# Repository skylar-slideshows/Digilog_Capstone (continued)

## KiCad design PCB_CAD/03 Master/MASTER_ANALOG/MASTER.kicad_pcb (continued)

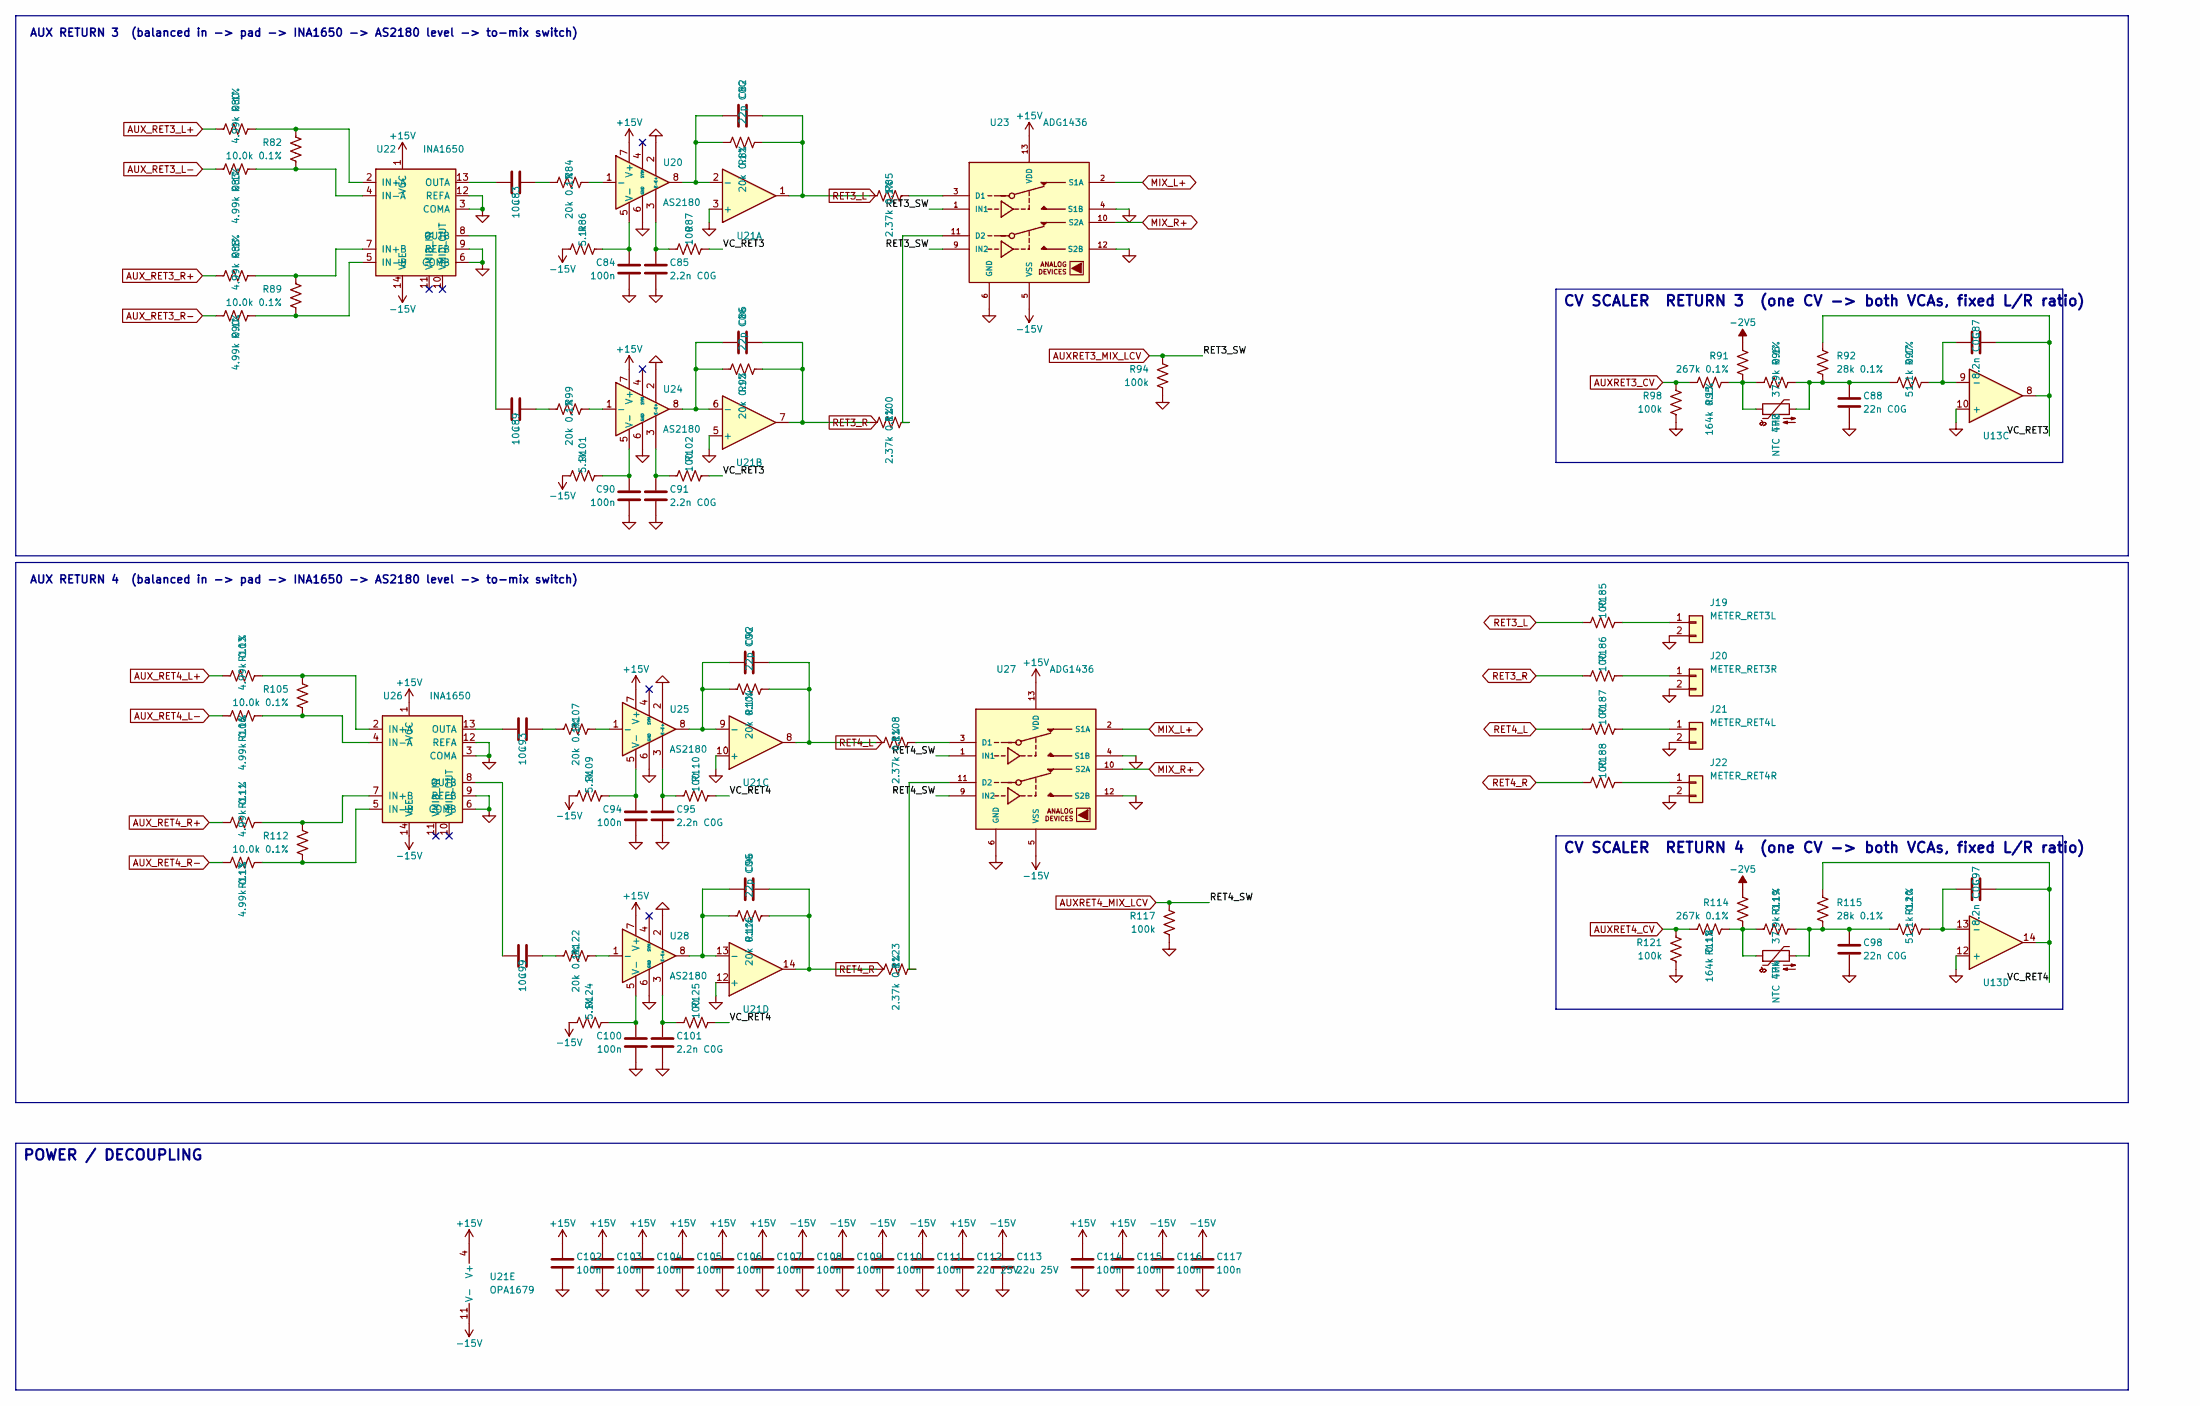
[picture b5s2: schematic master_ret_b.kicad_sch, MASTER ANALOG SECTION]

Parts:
C82, C86, C92, C96: 22p C0G; C_0603_1608Metric; LCSC C105620
C83, C89, C93, C99: 10u; CP_Elec_6.3x5.4_Nichicon; LCSC C340735
C84, C90, C94, C100, C102, C103, C104, C105, C106, C107, C108, C109, C110, C111, C114, C115, C116, C117: 100n; C_0603_1608Metric; LCSC C1590
C85, C91, C95, C101: 2.2n C0G; C_0603_1608Metric; LCSC C107043
C87, C97: 8.2n C0G; C_0805_2012Metric; LCSC C296107
C88, C98: 22n C0G; C_1206_3216Metric; LCSC C105982
C112, C113: 22u 25V; C_1210_3225Metric; LCSC C21397
J19: METER_RET3L; PinHeader_1x02_P2.54mm_Vertical; LCSC dnp
J20: METER_RET3R; PinHeader_1x02_P2.54mm_Vertical; LCSC dnp
J21: METER_RET4L; PinHeader_1x02_P2.54mm_Vertical; LCSC dnp
J22: METER_RET4R; PinHeader_1x02_P2.54mm_Vertical; LCSC dnp
R80, R83, R88, R90, R103, R106, R111, R113: 4.99k 0.1%; R_0603_1608Metric; LCSC C190614
R81, R84, R93, R99, R104, R107, R116, R122: 20k 0.1%; R_0603_1608Metric; LCSC C190611
R82, R89, R105, R112: 10.0k 0.1%; R_0603_1608Metric; LCSC C95204
R85, R100, R108, R123: 2.37k 0.1%; R_0603_1608Metric; LCSC C50670507
R86, R101, R109, R124: 5.1k; R_0603_1608Metric; LCSC C122969
R87, R102, R110, R125, R185, R186, R187, R188: 100; R_0603_1608Metric; LCSC C122970
R91, R114: 267k 0.1%; R_0603_1608Metric; LCSC C861785
R92, R115: 28k 0.1%; R_0603_1608Metric; LCSC C705756
R94, R98, R117, R121: 100k; R_0603_1608Metric; LCSC C122538
R95, R118: 164k 0.1%; R_0805_2012Metric; LCSC C865214
R96, R119: 37.9k 0.1%; R_0603_1608Metric; LCSC C861362
R97, R120: 51.1k 0.1%; R_0603_1608Metric; LCSC C491138
TH3, TH4: NTC 47k; R_Axial_DIN0207_L6.3mm_D2.5mm_P2.54mm_Vertical; LCSC dnp
U13: OPA4197; SOIC-14_3.9x8.7mm_P1.27mm; LCSC C2058532
U20, U24, U25, U28: AS2180; PinSocket_1x08_P2.54mm_Vertical; LCSC dnp
U21: OPA1679; TSSOP-14_4.4x5mm_P0.65mm; LCSC C2057264
U22, U26: INA1650; TSSOP-14_4.4x5mm_P0.65mm; LCSC C553130
U23, U27: ADG1436; TSSOP-16_4.4x5mm_P0.65mm; LCSC C408899

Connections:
+15V: C102.1, C103.1, C104.1, C105.1, C106.1, C107.1, C112.1, C114.1, C115.1, U20.7 (V+), U21.4 (V+), U22.1 (VCC), U23.13 (VDD), U24.7 (V+), U25.7 (V+), U26.1 (VCC), U27.13 (VDD), U28.7 (V+); also elsewhere on the board
-2V5: R91.1, R114.1; also elsewhere on the board
-15V: C108.1, C109.1, C110.1, C111.1, C113.1, C116.1, C117.1, R86.1, R101.1, R109.1, R124.1, U21.11 (V-), U22.14 (VEE), U23.5 (VSS), U26.14 (VEE), U27.5 (VSS); also elsewhere on the board
/RETURNS 3-4/VC_RET3: C87.2, R87.2, R92.1, R102.2, U13.8
/RETURNS 3-4/VC_RET4: C97.2, R110.2, R115.1, R125.2, U13.14
AUXRET3_CV: R95.1, R98.1; also elsewhere on the board
AUXRET3_MIX_LCV: R94.1, U23.1 (IN1), U23.9 (IN2); also elsewhere on the board
AUXRET4_CV: R118.1, R121.1; also elsewhere on the board
AUXRET4_MIX_LCV: R117.1, U27.1 (IN1), U27.9 (IN2); also elsewhere on the board
AUX_RET3_L+: R80.1; also elsewhere on the board
AUX_RET3_L-: R83.1; also elsewhere on the board
AUX_RET3_R+: R88.1; also elsewhere on the board
AUX_RET3_R-: R90.1; also elsewhere on the board
AUX_RET4_L+: R103.1; also elsewhere on the board
AUX_RET4_L-: R106.1; also elsewhere on the board
AUX_RET4_R+: R111.1; also elsewhere on the board
AUX_RET4_R-: R113.1; also elsewhere on the board
GND: C84.2, C85.2, C88.2, C90.2, C91.2, C94.2, C95.2, C98.2, C100.2, C101.2, C102.2, C103.2, C104.2, C105.2, C106.2, C107.2, C108.2, C109.2, C110.2, C111.2, C112.2, C113.2, C114.2, C115.2, C116.2, C117.2, J19.2, J20.2, J21.2, J22.2, R94.2, R98.2, R117.2, R121.2, U13.10 (+), U13.12 (+), U20.2 (E+), U20.6 (GND), U21.3 (+), U21.5 (+), U21.10 (+), U21.12 (+), U22.3 (COMA), U22.6 (COMB), U22.9 (REFB), U22.12 (REFA), U23.4 (S1B), U23.6 (GND), U23.12 (S2B), U24.2 (E+), U24.6 (GND), U25.2 (E+), U25.6 (GND), U26.3 (COMA), U26.6 (COMB), U26.9 (REFB), U26.12 (REFA), U27.4 (S1B), U27.6 (GND), U27.12 (S2B), U28.2 (E+), U28.6 (GND); also elsewhere on the board
MIX_L+: U23.2 (S1A), U27.2 (S1A); also elsewhere on the board
MIX_R+: U23.10 (S2A), U27.10 (S2A); also elsewhere on the board
unnamed: C83.2, R84.1
unnamed: C88.1, R92.2, R96.2, R97.1, TH3.2
unnamed: C89.2, R99.1
unnamed: C93.2, R107.1
unnamed: C98.1, R115.2, R119.2, R120.1, TH4.2
unnamed: C99.2, R122.1
unnamed: J19.1, R185.2
unnamed: J20.1, R186.2
unnamed: J21.1, R187.2
unnamed: J22.1, R188.2
unnamed: R91.2, R95.2, R96.1, TH3.1
unnamed: R114.2, R118.2, R119.1, TH4.1
unnamed: C87.1, R97.2, U13.9 (-)
unnamed: C97.1, R120.2, U13.13 (-)
unnamed: R84.2, U20.1 (-)
unnamed: C85.1, R87.1, U20.3 (E-)
unnamed: C84.1, R86.2, U20.5 (V-)
unnamed: C82.1, R81.1, U20.8, U21.2 (-)
unnamed: C86.1, R93.1, U21.6 (-), U24.8
unnamed: C92.1, R104.1, U21.9 (-), U25.8
unnamed: C96.1, R116.1, U21.13 (-), U28.8
unnamed: R80.2, R82.1, U22.2 (IN+A)
unnamed: R88.2, R89.1, U22.7 (IN+B)
unnamed: R82.2, R83.2, U22.4 (IN-A)
unnamed: R89.2, R90.2, U22.5 (IN-B)
unnamed: C83.1, U22.13 (OUTA)
unnamed: C89.1, U22.8 (OUTB)
unnamed: R85.2, U23.3 (D1)
unnamed: R100.2, U23.11 (D2)
unnamed: R99.2, U24.1 (-)
unnamed: C91.1, R102.1, U24.3 (E-)
unnamed: C90.1, R101.2, U24.5 (V-)
unnamed: R107.2, U25.1 (-)
unnamed: C95.1, R110.1, U25.3 (E-)
unnamed: C94.1, R109.2, U25.5 (V-)
unnamed: R103.2, R105.1, U26.2 (IN+A)
unnamed: R111.2, R112.1, U26.7 (IN+B)
unnamed: R105.2, R106.2, U26.4 (IN-A)
unnamed: R112.2, R113.2, U26.5 (IN-B)
unnamed: C93.1, U26.13 (OUTA)
unnamed: C99.1, U26.8 (OUTB)
unnamed: R108.2, U27.3 (D1)
unnamed: R123.2, U27.11 (D2)
unnamed: R122.2, U28.1 (-)
unnamed: C101.1, R125.1, U28.3 (E-)
unnamed: C100.1, R124.2, U28.5 (V-)
RET3_L: C82.2, R81.2, R85.1, R185.1, U21.1; also elsewhere on the board
RET3_R: C86.2, R93.2, R100.1, R186.1, U21.7; also elsewhere on the board
RET4_L: C92.2, R104.2, R108.1, R187.1, U21.8; also elsewhere on the board
RET4_R: C96.2, R116.2, R123.1, R188.1, U21.14; also elsewhere on the board

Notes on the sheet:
POWER / DECOUPLING
AUX RETURN 4 (balanced in -> pad -> INA1650 -> AS2180 level -> to-mix switch)
CV SCALER RETURN 4 (one CV -> both VCAs, fixed L/R ratio)
AUX RETURN 3 (balanced in -> pad -> INA1650 -> AS2180 level -> to-mix switch)
CV SCALER RETURN 3 (one CV -> both VCAs, fixed L/R ratio)

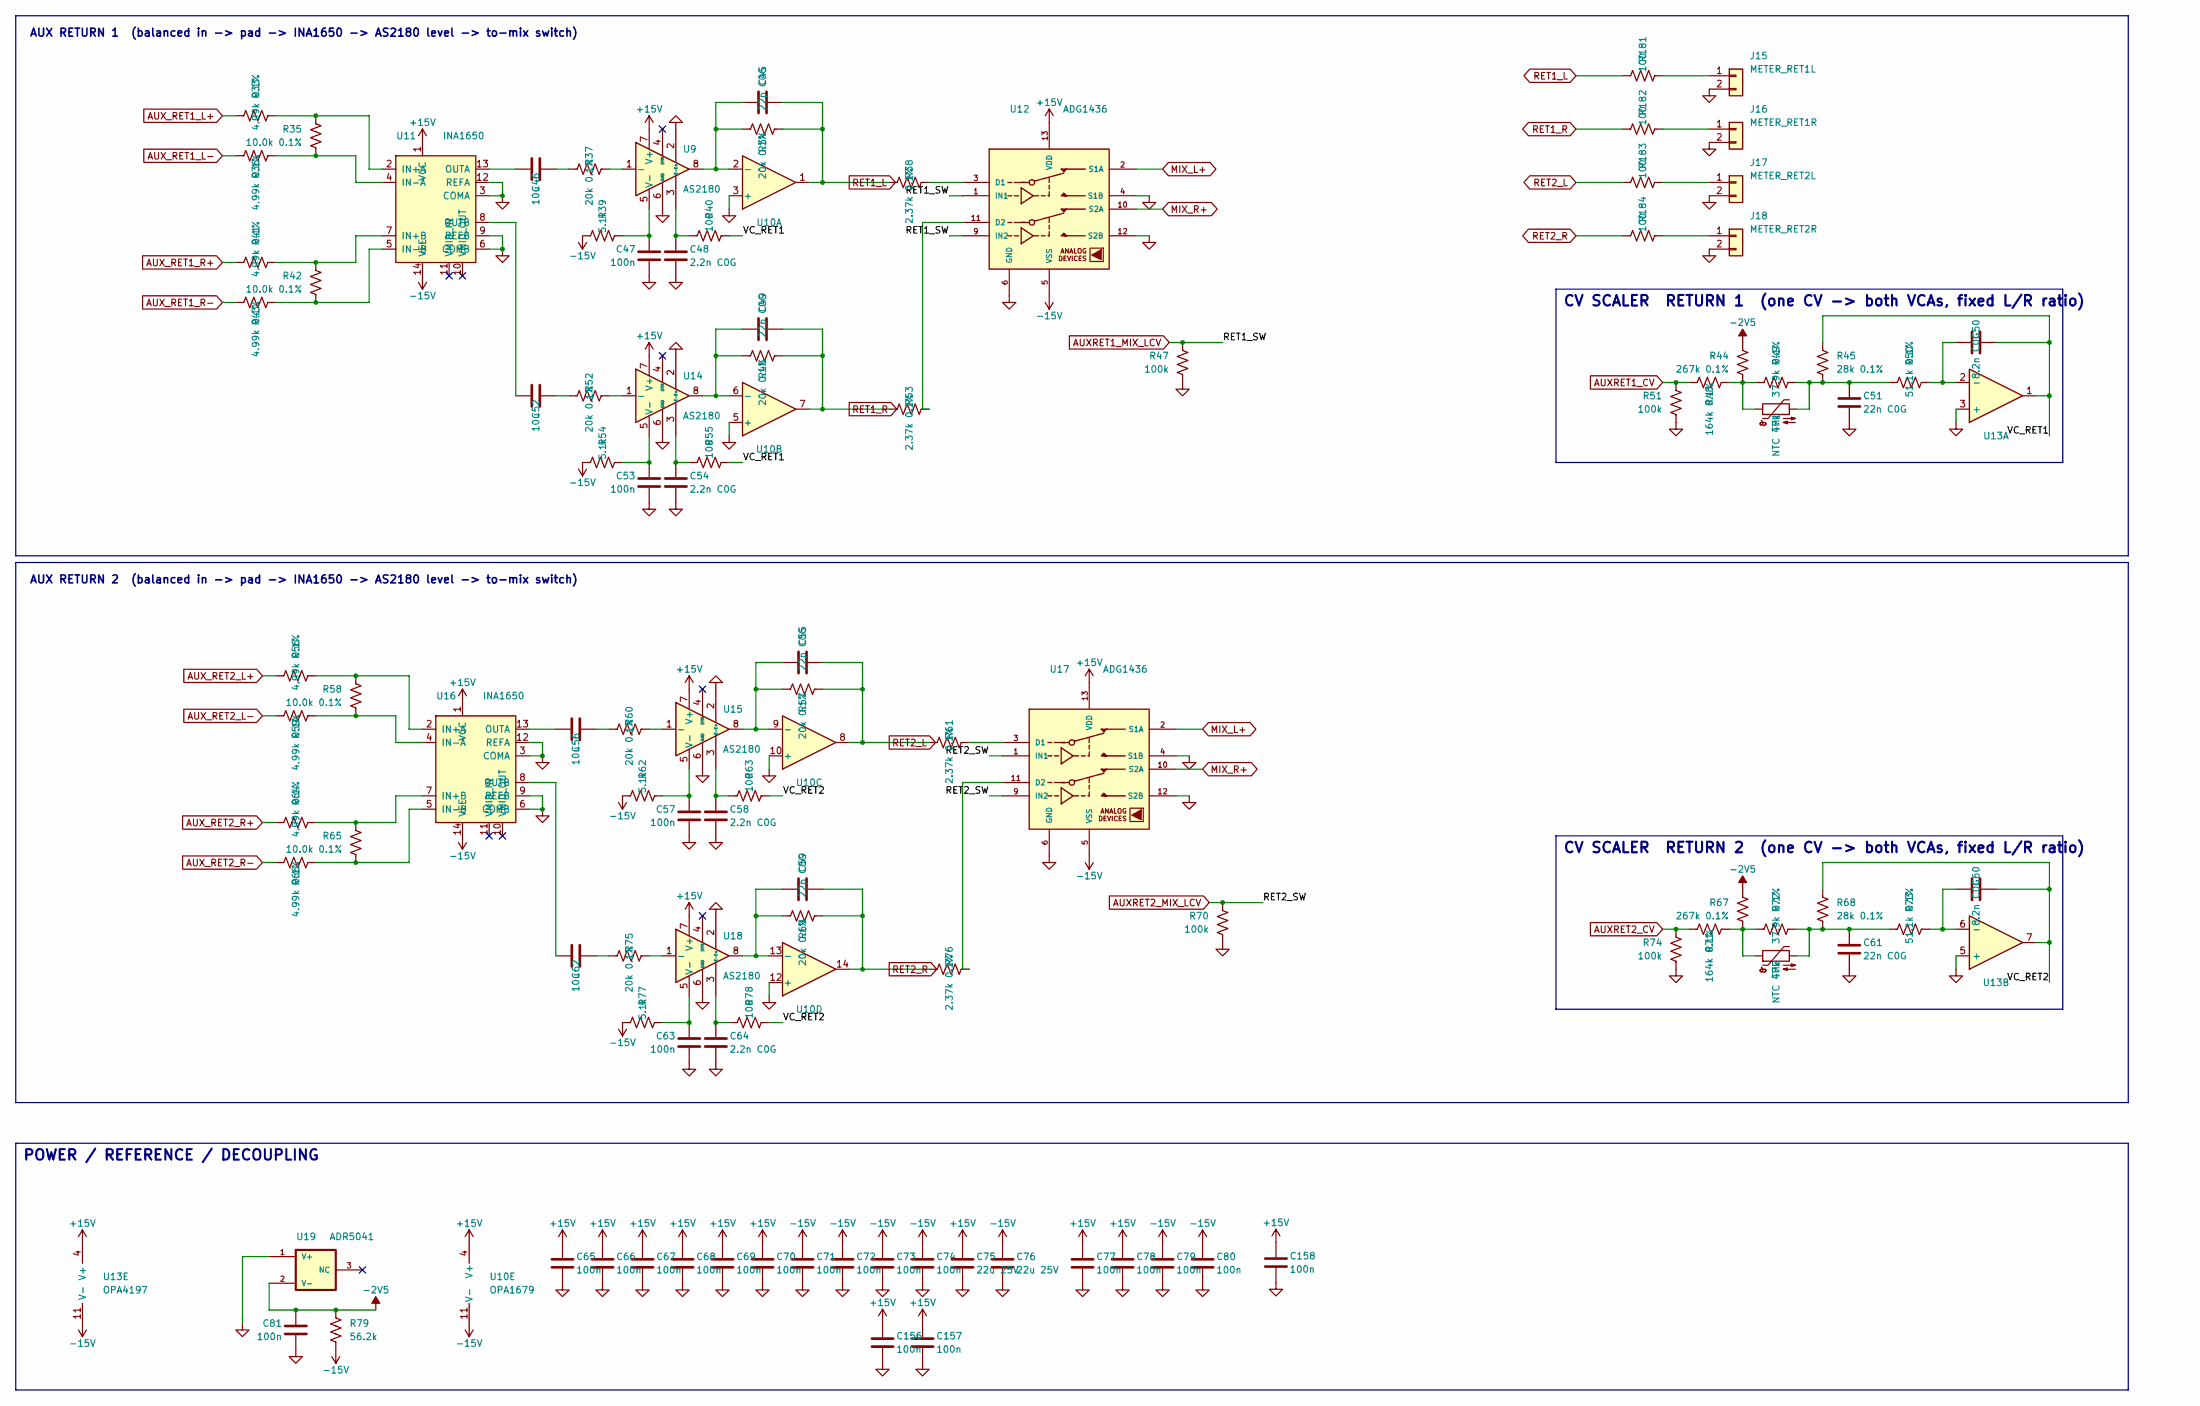
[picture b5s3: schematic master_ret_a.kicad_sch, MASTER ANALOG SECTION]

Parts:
C45, C49, C55, C59: 22p C0G; C_0603_1608Metric; LCSC C105620
C46, C52, C56, C62: 10u; CP_Elec_6.3x5.4_Nichicon; LCSC C340735
C47, C53, C57, C63, C65, C66, C67, C68, C69, C70, C71, C72, C73, C74, C77, C78, C79, C80, C81, C156, C157, C158: 100n; C_0603_1608Metric; LCSC C1590
C48, C54, C58, C64: 2.2n C0G; C_0603_1608Metric; LCSC C107043
C50, C60: 8.2n C0G; C_0805_2012Metric; LCSC C296107
C51, C61: 22n C0G; C_1206_3216Metric; LCSC C105982
C75, C76: 22u 25V; C_1210_3225Metric; LCSC C21397
J15: METER_RET1L; PinHeader_1x02_P2.54mm_Vertical; LCSC dnp
J16: METER_RET1R; PinHeader_1x02_P2.54mm_Vertical; LCSC dnp
J17: METER_RET2L; PinHeader_1x02_P2.54mm_Vertical; LCSC dnp
J18: METER_RET2R; PinHeader_1x02_P2.54mm_Vertical; LCSC dnp
R33, R36, R41, R43, R56, R59, R64, R66: 4.99k 0.1%; R_0603_1608Metric; LCSC C190614
R34, R37, R46, R52, R57, R60, R69, R75: 20k 0.1%; R_0603_1608Metric; LCSC C190611
R35, R42, R58, R65: 10.0k 0.1%; R_0603_1608Metric; LCSC C95204
R38, R53, R61, R76: 2.37k 0.1%; R_0603_1608Metric; LCSC C50670507
R39, R54, R62, R77: 5.1k; R_0603_1608Metric; LCSC C122969
R40, R55, R63, R78, R181, R182, R183, R184: 100; R_0603_1608Metric; LCSC C122970
R44, R67: 267k 0.1%; R_0603_1608Metric; LCSC C861785
R45, R68: 28k 0.1%; R_0603_1608Metric; LCSC C705756
R47, R51, R70, R74: 100k; R_0603_1608Metric; LCSC C122538
R48, R71: 164k 0.1%; R_0805_2012Metric; LCSC C865214
R49, R72: 37.9k 0.1%; R_0603_1608Metric; LCSC C861362
R50, R73: 51.1k 0.1%; R_0603_1608Metric; LCSC C491138
R79: 56.2k; R_0603_1608Metric; LCSC C23080
TH1, TH2: NTC 47k; R_Axial_DIN0207_L6.3mm_D2.5mm_P2.54mm_Vertical; LCSC dnp
U9, U14, U15, U18: AS2180; PinSocket_1x08_P2.54mm_Vertical; LCSC dnp
U10: OPA1679; TSSOP-14_4.4x5mm_P0.65mm; LCSC C2057264
U11, U16: INA1650; TSSOP-14_4.4x5mm_P0.65mm; LCSC C553130
U12, U17: ADG1436; TSSOP-16_4.4x5mm_P0.65mm; LCSC C408899
U13: OPA4197; SOIC-14_3.9x8.7mm_P1.27mm; LCSC C2058532
U19: ADR5041; SOT-23; LCSC C2686108

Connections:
+15V: C65.1, C66.1, C67.1, C68.1, C69.1, C70.1, C75.1, C77.1, C78.1, C156.1, C157.1, C158.1, U9.7 (V+), U10.4 (V+), U11.1 (VCC), U12.13 (VDD), U13.4 (V+), U14.7 (V+), U15.7 (V+), U16.1 (VCC), U17.13 (VDD), U18.7 (V+); also elsewhere on the board
-2V5: C81.1, R44.1, R67.1, R79.1, U19.2 (V-); also elsewhere on the board
-15V: C71.1, C72.1, C73.1, C74.1, C76.1, C79.1, C80.1, R39.1, R54.1, R62.1, R77.1, R79.2, U10.11 (V-), U11.14 (VEE), U12.5 (VSS), U13.11 (V-), U16.14 (VEE), U17.5 (VSS); also elsewhere on the board
/RETURNS 1-2/VC_RET1: C50.2, R40.2, R45.1, R55.2, U13.1
/RETURNS 1-2/VC_RET2: C60.2, R63.2, R68.1, R78.2, U13.7
AUXRET1_CV: R48.1, R51.1; also elsewhere on the board
AUXRET1_MIX_LCV: R47.1, U12.1 (IN1), U12.9 (IN2); also elsewhere on the board
AUXRET2_CV: R71.1, R74.1; also elsewhere on the board
AUXRET2_MIX_LCV: R70.1, U17.1 (IN1), U17.9 (IN2); also elsewhere on the board
AUX_RET1_L+: R33.1; also elsewhere on the board
AUX_RET1_L-: R36.1; also elsewhere on the board
AUX_RET1_R+: R41.1; also elsewhere on the board
AUX_RET1_R-: R43.1; also elsewhere on the board
AUX_RET2_L+: R56.1; also elsewhere on the board
AUX_RET2_L-: R59.1; also elsewhere on the board
AUX_RET2_R+: R64.1; also elsewhere on the board
AUX_RET2_R-: R66.1; also elsewhere on the board
GND: C47.2, C48.2, C51.2, C53.2, C54.2, C57.2, C58.2, C61.2, C63.2, C64.2, C65.2, C66.2, C67.2, C68.2, C69.2, C70.2, C71.2, C72.2, C73.2, C74.2, C75.2, C76.2, C77.2, C78.2, C79.2, C80.2, C81.2, C156.2, C157.2, C158.2, J15.2, J16.2, J17.2, J18.2, R47.2, R51.2, R70.2, R74.2, U9.2 (E+), U9.6 (GND), U10.3 (+), U10.5 (+), U10.10 (+), U10.12 (+), U11.3 (COMA), U11.6 (COMB), U11.9 (REFB), U11.12 (REFA), U12.4 (S1B), U12.6 (GND), U12.12 (S2B), U13.3 (+), U13.5 (+), U14.2 (E+), U14.6 (GND), U15.2 (E+), U15.6 (GND), U16.3 (COMA), U16.6 (COMB), U16.9 (REFB), U16.12 (REFA), U17.4 (S1B), U17.6 (GND), U17.12 (S2B), U18.2 (E+), U18.6 (GND), U19.1 (V+); also elsewhere on the board
MIX_L+: U12.2 (S1A), U17.2 (S1A); also elsewhere on the board
MIX_R+: U12.10 (S2A), U17.10 (S2A); also elsewhere on the board
unnamed: C46.2, R37.1
unnamed: C51.1, R45.2, R49.2, R50.1, TH1.2
unnamed: C52.2, R52.1
unnamed: C56.2, R60.1
unnamed: C61.1, R68.2, R72.2, R73.1, TH2.2
unnamed: C62.2, R75.1
unnamed: J15.1, R181.2
unnamed: J16.1, R182.2
unnamed: J17.1, R183.2
unnamed: J18.1, R184.2
unnamed: R44.2, R48.2, R49.1, TH1.1
unnamed: R67.2, R71.2, R72.1, TH2.1
unnamed: R37.2, U9.1 (-)
unnamed: C48.1, R40.1, U9.3 (E-)
unnamed: C47.1, R39.2, U9.5 (V-)
unnamed: C45.1, R34.1, U9.8, U10.2 (-)
unnamed: C49.1, R46.1, U10.6 (-), U14.8
unnamed: C55.1, R57.1, U10.9 (-), U15.8
unnamed: C59.1, R69.1, U10.13 (-), U18.8
unnamed: R33.2, R35.1, U11.2 (IN+A)
unnamed: R41.2, R42.1, U11.7 (IN+B)
unnamed: R35.2, R36.2, U11.4 (IN-A)
unnamed: R42.2, R43.2, U11.5 (IN-B)
unnamed: C46.1, U11.13 (OUTA)
unnamed: C52.1, U11.8 (OUTB)
unnamed: R38.2, U12.3 (D1)
unnamed: R53.2, U12.11 (D2)
unnamed: C50.1, R50.2, U13.2 (-)
unnamed: C60.1, R73.2, U13.6 (-)
unnamed: R52.2, U14.1 (-)
unnamed: C54.1, R55.1, U14.3 (E-)
unnamed: C53.1, R54.2, U14.5 (V-)
unnamed: R60.2, U15.1 (-)
unnamed: C58.1, R63.1, U15.3 (E-)
unnamed: C57.1, R62.2, U15.5 (V-)
unnamed: R56.2, R58.1, U16.2 (IN+A)
unnamed: R64.2, R65.1, U16.7 (IN+B)
unnamed: R58.2, R59.2, U16.4 (IN-A)
unnamed: R65.2, R66.2, U16.5 (IN-B)
unnamed: C56.1, U16.13 (OUTA)
unnamed: C62.1, U16.8 (OUTB)
unnamed: R61.2, U17.3 (D1)
unnamed: R76.2, U17.11 (D2)
unnamed: R75.2, U18.1 (-)
unnamed: C64.1, R78.1, U18.3 (E-)
unnamed: C63.1, R77.2, U18.5 (V-)
RET1_L: C45.2, R34.2, R38.1, R181.1, U10.1; also elsewhere on the board
RET1_R: C49.2, R46.2, R53.1, R182.1, U10.7; also elsewhere on the board
RET2_L: C55.2, R57.2, R61.1, R183.1, U10.8; also elsewhere on the board
RET2_R: C59.2, R69.2, R76.1, R184.1, U10.14; also elsewhere on the board

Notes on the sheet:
AUX RETURN 1 (balanced in -> pad -> INA1650 -> AS2180 level -> to-mix switch)
AUX RETURN 2 (balanced in -> pad -> INA1650 -> AS2180 level -> to-mix switch)
POWER / REFERENCE / DECOUPLING
CV SCALER RETURN 1 (one CV -> both VCAs, fixed L/R ratio)
CV SCALER RETURN 2 (one CV -> both VCAs, fixed L/R ratio)

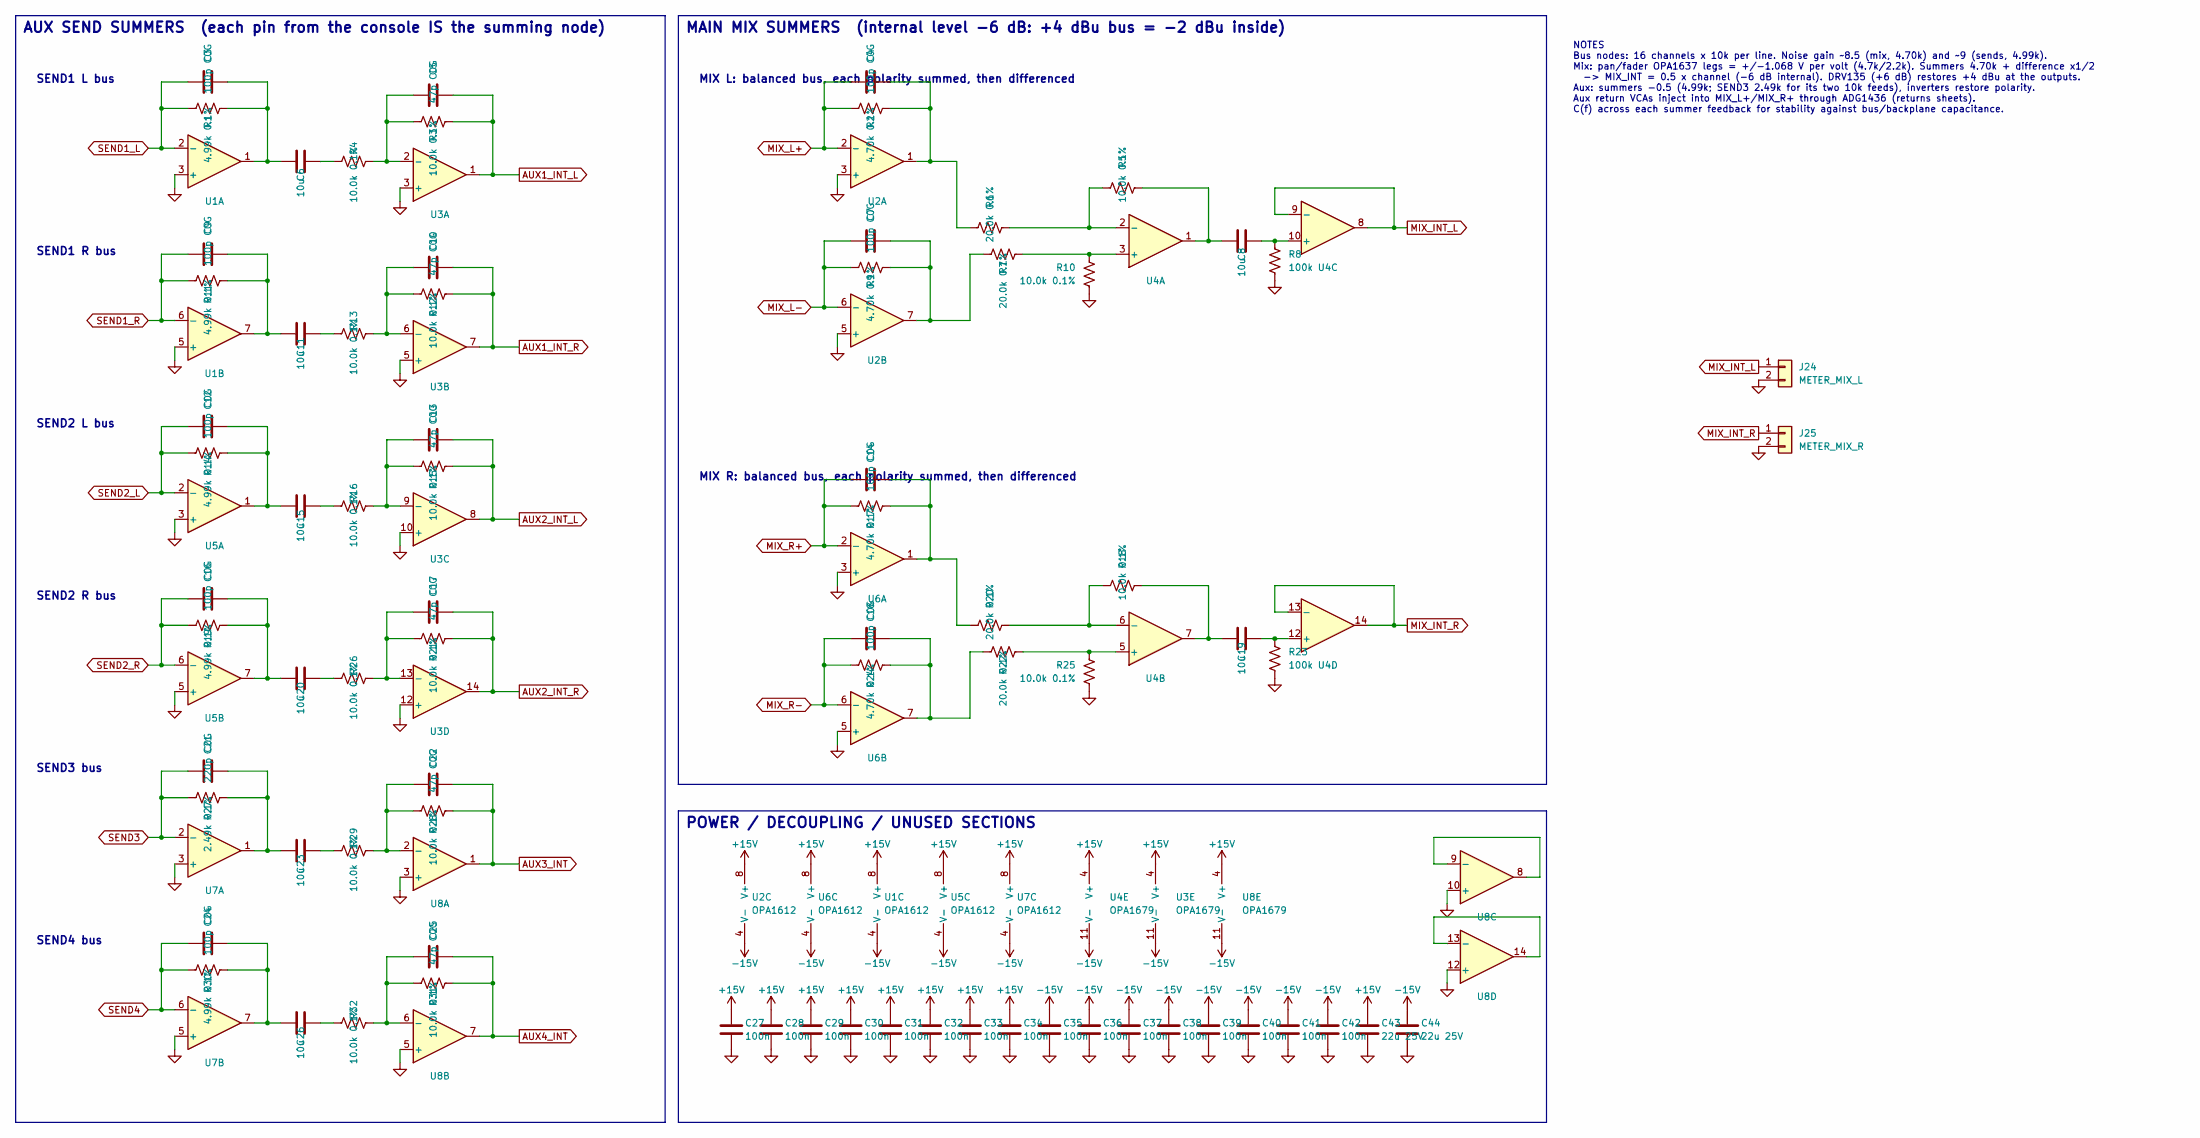
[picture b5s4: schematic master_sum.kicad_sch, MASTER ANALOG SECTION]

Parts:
C3, C4, C7, C9, C12, C14, C16, C18, C24: 100p C0G; C_0603_1608Metric; LCSC C14665
C5, C10, C13, C17, C22, C25: 47p C0G; C_0603_1608Metric; LCSC C105622
C6, C8, C11, C15, C19, C20, C23, C26: 10u; CP_Elec_6.3x5.4_Nichicon; LCSC C340735
C21: 220p C0G; C_0603_1608Metric; LCSC C694226
C27, C28, C29, C30, C31, C32, C33, C34, C35, C36, C37, C38, C39, C40, C41, C42: 100n; C_0603_1608Metric; LCSC C1590
C43, C44: 22u 25V; C_1210_3225Metric; LCSC C21397
J24: METER_MIX_L; PinHeader_1x02_P2.54mm_Vertical; LCSC dnp
J25: METER_MIX_R; PinHeader_1x02_P2.54mm_Vertical; LCSC dnp
R1, R11, R14, R19, R30: 4.99k 0.1%; R_0603_1608Metric; LCSC C190614
R2, R9, R17, R24: 4.70k 0.1%; R_0603_1608Metric; LCSC C328429
R3, R4, R5, R10, R12, R13, R15, R16, R18, R21, R25, R26, R28, R29, R31, R32: 10.0k 0.1%; R_0603_1608Metric; LCSC C95204
R6, R7, R20, R22: 20.0k 0.1%; R_0603_1608Metric; LCSC C190611
R8, R23: 100k; R_0603_1608Metric; LCSC C122538
R27: 2.49k 0.1%; R_0603_1608Metric; LCSC C319797
U1, U2, U5, U6, U7: OPA1612; SOIC-8_3.9x4.9mm_P1.27mm; LCSC C94590
U3, U4, U8: OPA1679; TSSOP-14_4.4x5mm_P0.65mm; LCSC C2057264

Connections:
+15V: C27.1, C28.1, C29.1, C30.1, C31.1, C32.1, C33.1, C34.1, C43.1, U1.8 (V+), U2.8 (V+), U3.4 (V+), U4.4 (V+), U5.8 (V+), U6.8 (V+), U7.8 (V+), U8.4 (V+); also elsewhere on the board
-15V: C35.1, C36.1, C37.1, C38.1, C39.1, C40.1, C41.1, C42.1, C44.1, U1.4 (V-), U2.4 (V-), U3.11 (V-), U4.11 (V-), U5.4 (V-), U6.4 (V-), U7.4 (V-), U8.11 (V-); also elsewhere on the board
AUX1_INT_L: C5.2, R3.2, U3.1; also elsewhere on the board
AUX1_INT_R: C10.2, R12.2, U3.7; also elsewhere on the board
AUX2_INT_L: C13.2, R15.2, U3.8; also elsewhere on the board
AUX2_INT_R: C17.2, R21.2, U3.14; also elsewhere on the board
AUX3_INT: C22.2, R28.2, U8.1; also elsewhere on the board
AUX4_INT: C25.2, R31.2, U8.7; also elsewhere on the board
GND: C27.2, C28.2, C29.2, C30.2, C31.2, C32.2, C33.2, C34.2, C35.2, C36.2, C37.2, C38.2, C39.2, C40.2, C41.2, C42.2, C43.2, C44.2, J24.2, J25.2, R8.2, R10.2, R23.2, R25.2, U1.3 (+), U1.5 (+), U2.3 (+), U2.5 (+), U3.3 (+), U3.5 (+), U3.10 (+), U3.12 (+), U5.3 (+), U5.5 (+), U6.3 (+), U6.5 (+), U7.3 (+), U7.5 (+), U8.3 (+), U8.5 (+), U8.10 (+), U8.12 (+); also elsewhere on the board
MIX_INT_L: J24.1, U4.8, U4.9 (-); also elsewhere on the board
MIX_INT_R: J25.1, U4.13 (-), U4.14; also elsewhere on the board
MIX_L+: C4.1, R2.1, U2.2 (-); also elsewhere on the board
MIX_L-: C7.1, R9.1, U2.6 (-); also elsewhere on the board
MIX_R+: C14.1, R17.1, U6.2 (-); also elsewhere on the board
MIX_R-: C18.1, R24.1, U6.6 (-); also elsewhere on the board
unnamed: C3.2, C6.1, R1.2, U1.1
unnamed: C4.2, R2.2, R6.1, U2.1
unnamed: C6.2, R4.1
unnamed: C7.2, R7.1, R9.2, U2.7
unnamed: C8.1, R5.2, U4.1
unnamed: C9.2, C11.1, R11.2, U1.7
unnamed: C11.2, R13.1
unnamed: C12.2, C15.1, R14.2, U5.1
unnamed: C14.2, R17.2, R20.1, U6.1
unnamed: C15.2, R16.1
unnamed: C16.2, C20.1, R19.2, U5.7
unnamed: C18.2, R22.1, R24.2, U6.7
unnamed: C19.1, R18.2, U4.7
unnamed: C20.2, R26.1
unnamed: C21.2, C23.1, R27.2, U7.1
unnamed: C23.2, R29.1
unnamed: C24.2, C26.1, R30.2, U7.7
unnamed: C26.2, R32.1
unnamed: C5.1, R3.1, R4.2, U3.2 (-)
unnamed: C10.1, R12.1, R13.2, U3.6 (-)
unnamed: C13.1, R15.1, R16.2, U3.9 (-)
unnamed: C17.1, R21.1, R26.2, U3.13 (-)
unnamed: R7.2, R10.1, U4.3 (+)
unnamed: R5.1, R6.2, U4.2 (-)
unnamed: R22.2, R25.1, U4.5 (+)
unnamed: R18.1, R20.2, U4.6 (-)
unnamed: C8.2, R8.1, U4.10 (+)
unnamed: C19.2, R23.1, U4.12 (+)
unnamed: C22.1, R28.1, R29.2, U8.2 (-)
unnamed: C25.1, R31.1, R32.2, U8.6 (-)
unnamed: U8.8, U8.9 (-)
unnamed: U8.13 (-), U8.14
SEND1_L: C3.1, R1.1, U1.2 (-); also elsewhere on the board
SEND1_R: C9.1, R11.1, U1.6 (-); also elsewhere on the board
SEND2_L: C12.1, R14.1, U5.2 (-); also elsewhere on the board
SEND2_R: C16.1, R19.1, U5.6 (-); also elsewhere on the board
SEND3: C21.1, R27.1, U7.2 (-); also elsewhere on the board
SEND4: C24.1, R30.1, U7.6 (-); also elsewhere on the board

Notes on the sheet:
SEND3 bus
SEND2 R bus
SEND1 L bus
MIX L: balanced bus, each polarity summed, then differenced
SEND1 R bus
MAIN MIX SUMMERS (internal level -6 dB: +4 dBu bus = -2 dBu inside)
NOTES Bus nodes: 16 channels x 10k per line. Noise gain ~8.5 (mix, 4.70k) and ~9 (sends, 4.99k). Mix: pan/fader OPA1637 legs = +/-1.068 V per volt (4.7k/2.2k). Summers 4.70k + difference x1/2 -> MIX_INT = 0.5 x channel (-6 dB internal). DRV135 (+6 dB) restores +4 dBu at the outputs. Aux: summers -0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
SEND4 bus
AUX SEND SUMMERS (each pin from the console IS the summing node)
MIX R: balanced bus, each polarity summed, then differenced
SEND2 L bus
POWER / DECOUPLING / UNUSED SECTIONS
